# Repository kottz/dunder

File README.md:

# 🖱️ Dunder
A fully* functioning mouse implemented from scratch.

# _**Intended features**_
-----------
- Button functionality built into the scroll wheel - One should be able to click the scroll wheel.
- additional buttons found on the mouse: 
1. Mouse sensitivity buttons - one to increase sensitivity and one to reduce it.
2. forward/back buttons - two macro buttons for the user to bind.

- Led user settings.
- Custom shell. 3D printed.

# _**Design overview**_
-----------

_Buttons provide:_
1. Right and left click.
2. Mouse wheel click.
3. Forward and backwards, which are two macro buttons.
4. Sense up and sense down, two buttons to control mouse sensitivity.

_Sensor provide position data._

_PSU provide:_
1. 3.3V to the buttons and mcu.
2. 1.9V to the sensor.

# _**Circuit design**_
-----------
_**KiCAD diagram**_
-----------

# _**Board design**_
_**KiCAD model**_
-----------

_**3D model**_
-----------

_**Real board**_
-----------
##### Version 1

##### Version 2

# _**Custom case**_
-----------
The case was designed from scratch using Fusion 360.

# _**Demo**_
-----------
##### Demo of mouse functionality

##### Demo of 3D printed case

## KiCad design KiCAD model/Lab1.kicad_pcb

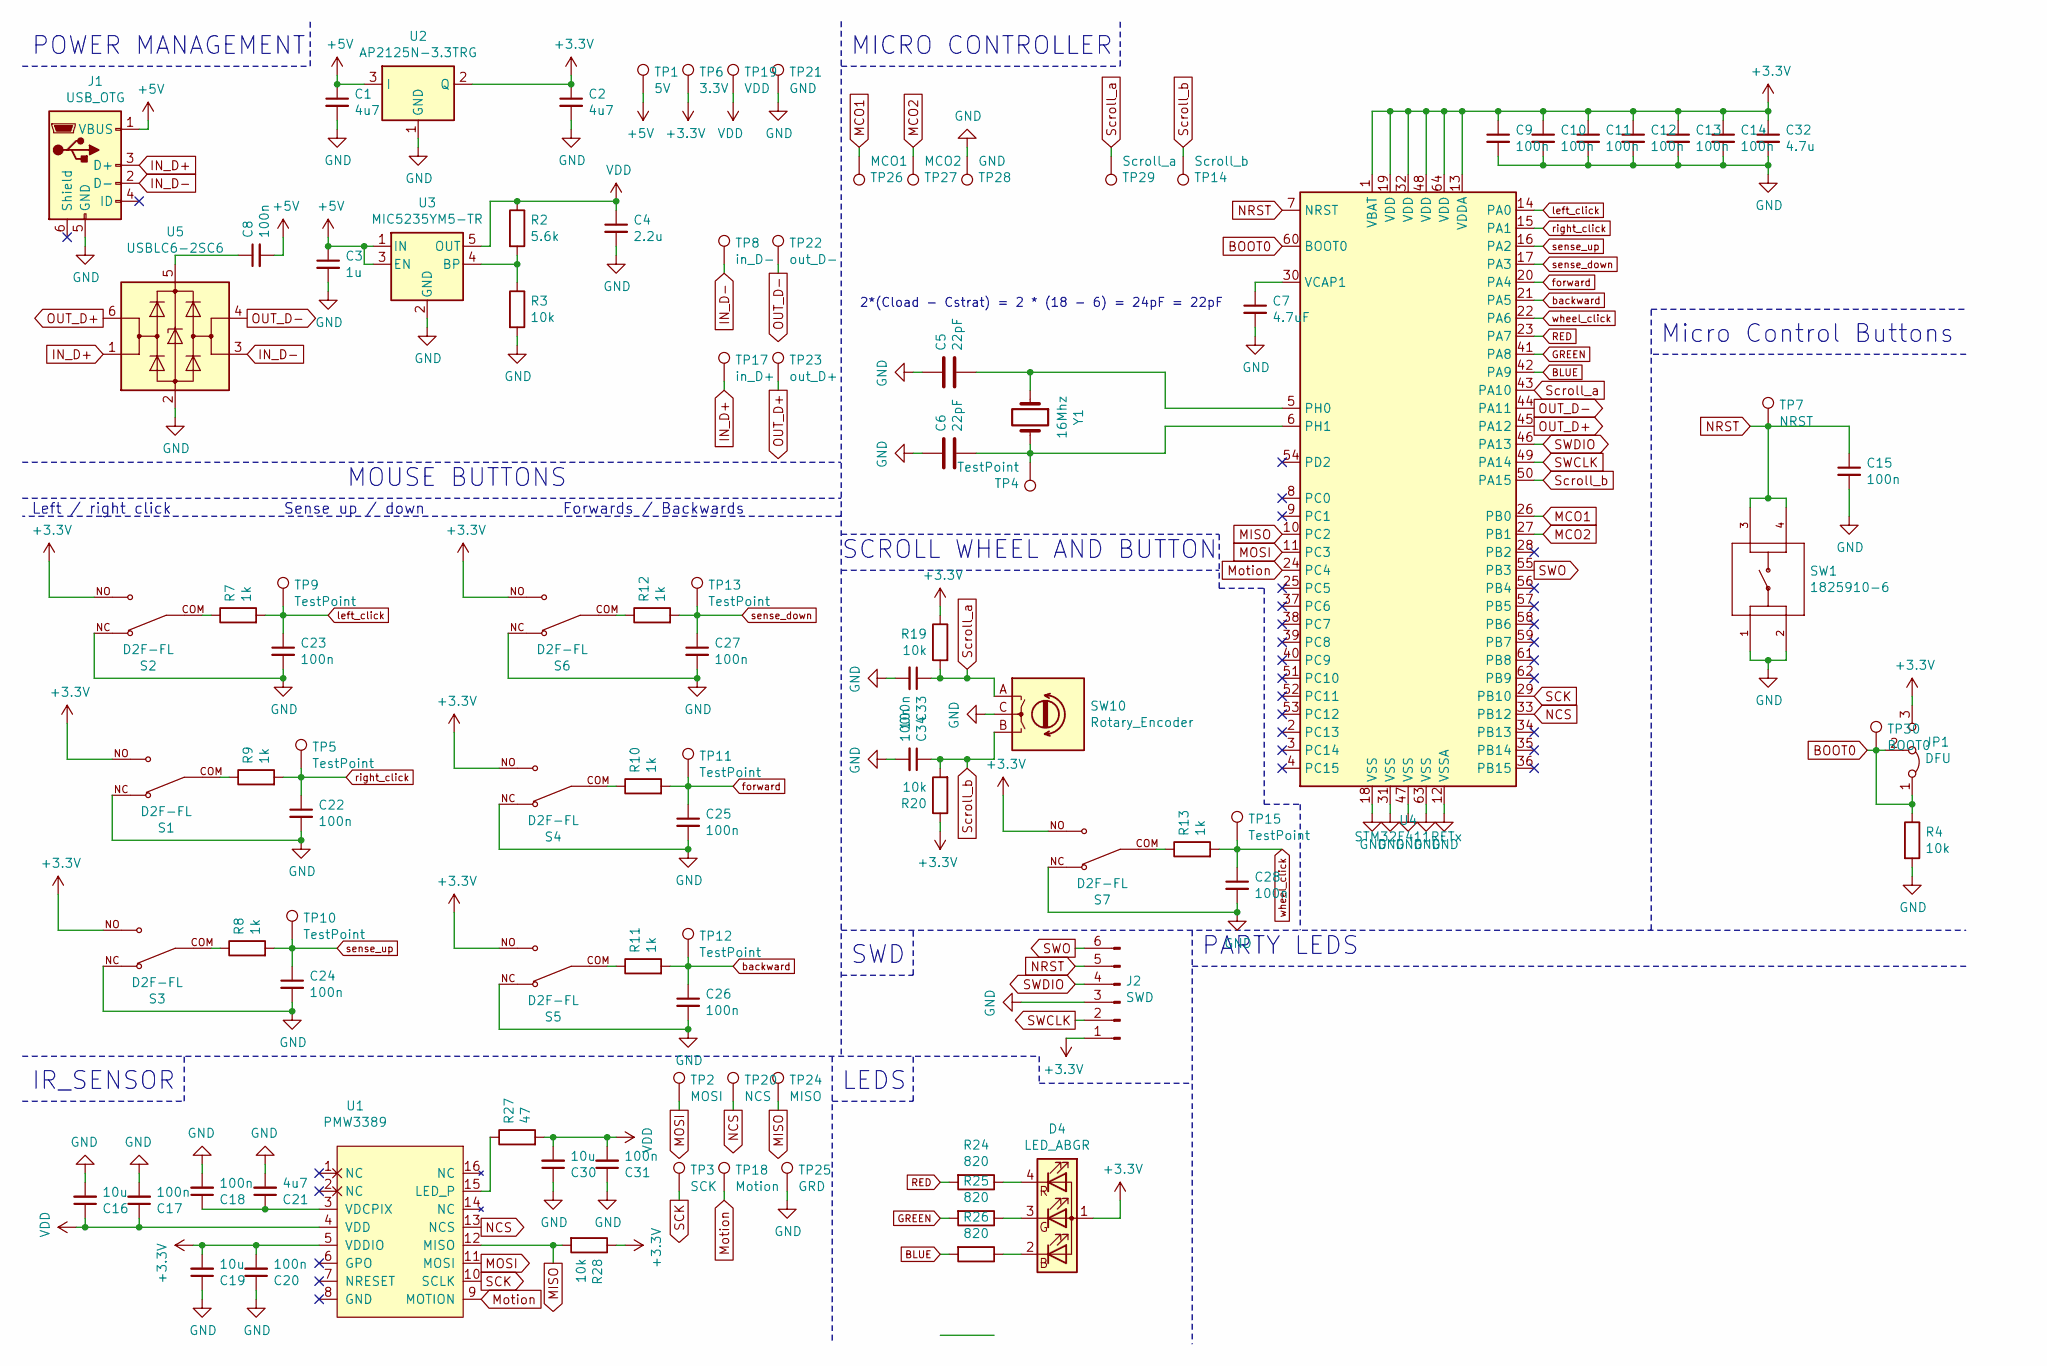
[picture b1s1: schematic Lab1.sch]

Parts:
C1, C2, C21: 4u7; C_0805_2012Metric_Pad1.18x1.45mm_HandSolder
C3: 1u; C_0805_2012Metric_Pad1.18x1.45mm_HandSolder
C4: 2.2u; C_0805_2012Metric_Pad1.18x1.45mm_HandSolder
C5, C6: 22pF; C_0805_2012Metric_Pad1.18x1.45mm_HandSolder
C7: 4.7uF; C_0805_2012Metric_Pad1.18x1.45mm_HandSolder
C8, C9, C10, C11, C12, C13, C14, C15, C17, C18, C20, C22, C23, C24, C25, C26, C27, C28, C31, C33, C34: 100n; C_0805_2012Metric_Pad1.18x1.45mm_HandSolder
C16, C19, C30: 10u; C_0805_2012Metric_Pad1.18x1.45mm_HandSolder
C32: 4.7u; C_0805_2012Metric_Pad1.18x1.45mm_HandSolder
D4: LED_ABGR; LED_RGB_1210_RND_135-00251
J1: USB_OTG; USB_Micro-B_Wuerth_614105150721_Vertical
J2: SWD; PinHeader_1x06_P2.54mm_Vertical
JP1: DFU; PinHeader_1x03_P2.54mm_Vertical
R2: 5.6k; R_0805_2012Metric_Pad1.20x1.40mm_HandSolder
R3, R4, R19, R20, R28: 10k; R_0805_2012Metric_Pad1.20x1.40mm_HandSolder
R7, R8, R9, R10, R11, R12, R13: 1k; R_0805_2012Metric_Pad1.20x1.40mm_HandSolder
R24, R25, R26: 820; R_0805_2012Metric_Pad1.20x1.40mm_HandSolder
R27: 47; R_0805_2012Metric_Pad1.20x1.40mm_HandSolder
S1, S2, S3, S4, S5, S6, S7: D2F-FL; SW_D2F-FL; PARTREV N/A
SW1: 1825910-6; SW_1825910-6-4
SW10: Rotary_Encoder; EC10E1220505
TP1: 5V; TestPoint_Pad_1.5x1.5mm
TP2: MOSI; TestPoint_Pad_1.5x1.5mm
TP3: SCK; TestPoint_Pad_1.5x1.5mm
TP4, TP5, TP9, TP10, TP11, TP12, TP13, TP15: TestPoint; TestPoint_Pad_1.5x1.5mm
TP6: 3.3V; TestPoint_Pad_1.5x1.5mm
TP7: NRST; TestPoint_Pad_1.5x1.5mm
TP8: in_D-; TestPoint_Pad_1.5x1.5mm
TP14: Scroll_b; TestPoint_Pad_1.5x1.5mm
TP17: in_D+; TestPoint_Pad_1.5x1.5mm
TP18: Motion; TestPoint_Pad_1.5x1.5mm
TP19: VDD; TestPoint_Pad_1.5x1.5mm
TP20: NCS; TestPoint_Pad_1.5x1.5mm
TP21, TP28: GND; TestPoint_Pad_1.5x1.5mm
TP22: out_D-; TestPoint_Pad_1.5x1.5mm
TP23: out_D+; TestPoint_Pad_1.5x1.5mm
TP24: MISO; TestPoint_Pad_1.5x1.5mm
TP25: GRD; TestPoint_Pad_1.5x1.5mm
TP26: MCO1; TestPoint_Pad_1.5x1.5mm
TP27: MCO2; TestPoint_Pad_1.5x1.5mm
TP29: Scroll_a; TestPoint_Pad_1.5x1.5mm
TP30: BOOT0; TestPoint_Pad_1.5x1.5mm
U1: PMW3389
U2: AP2125N-3.3TRG; SOT-23_Handsoldering
U3: MIC5235YM5-TR; SOT-23-5_HandSoldering
U4: STM32F411RETx; LQFP-64_10x10mm_P0.5mm
U5: USBLC6-2SC6; SOT-23-6
Y1: 16Mhz; Crystal_SMD_HC49-SD_HandSoldering

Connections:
+3V3: C2.1, C9.1, C10.1, C11.1, C12.1, C13.1, C14.1, C19.2, C20.2, C32.1, D4.1 (A), J2.1, JP1.3 (B), R19.1, R20.1, R28.1, S1.NO, S2.NO, S3.NO, S4.NO, S5.NO, S6.NO, S7.NO, TP6.1, U1.5 (VDDIO), U2.2 (Q), U4.1 (VBAT), U4.13 (VDDA), U4.19 (VDD), U4.32 (VDD), U4.48 (VDD), U4.64 (VDD)
+5V: C1.1, C3.1, C8.2, J1.1 (VBUS), TP1.1, U2.3 (I), U3.1 (IN), U3.3 (EN)
BLUE: R26.2, U4.42 (PA9)
BOOT0: JP1.1 (A), JP1.2 (C), R4.1, TP30.1, U4.60 (BOOT0)
GND: C1.2, C2.2, C3.2, C4.2, C5.1, C6.1, C7.2, C9.2, C10.2, C11.2, C12.2, C13.2, C14.2, C15.2, C16.2, C17.2, C18.2, C19.1, C20.1, C21.2, C22.2, C23.2, C24.2, C25.2, C26.2, C27.2, C28.2, C30.1, C31.1, C32.2, C33.2, C34.2, J1.5 (GND), J2.3, R3.2, R4.2, S1.NC, S2.NC, S3.NC, S4.NC, S5.NC, S6.NC, S7.NC, SW1.1, SW1.2, SW10.C, TP21.1, TP25.1, TP28.1, U2.1 (GND), U3.2 (GND), U4.12 (VSSA), U4.18 (VSS), U4.31 (VSS), U4.47 (VSS), U4.63 (VSS), U5.2 (GND)
GREEN: R25.2, U4.41 (PA8)
IN_D+: J1.3 (D+), TP17.1, U5.1 (I/O1)
IN_D-: J1.2 (D-), TP8.1, U5.3 (I/O2)
MCO1: TP26.1, U4.26 (PB0)
MCO2: TP27.1, U4.27 (PB1)
MISO: R28.2, TP24.1, U1.12 (MISO), U4.10 (PC2)
MOSI: TP2.1, U1.11 (MOSI), U4.11 (PC3)
Motion: TP18.1, U1.9 (MOTION), U4.24 (PC4)
NCS: TP20.1, U1.13 (NCS), U4.33 (PB12)
NRST: C15.1, J2.5, SW1.3, SW1.4, TP7.1, U4.7 (NRST)
unnamed: C5.2, U4.5 (PH0), Y1.1
unnamed: C6.2, TP4.1, U4.6 (PH1), Y1.2
unnamed: C7.1, U4.30 (VCAP1)
unnamed: C8.1, U5.5 (VBUS)
unnamed: C18.1, C21.1, U1.3 (VDCPIX)
unnamed: D4.2 (BK), R26.1
unnamed: D4.3 (GK), R25.1
unnamed: D4.4 (RK), R24.1
unnamed: R2.2, R3.1, U3.4 (BP)
unnamed: R7.1, S2.COM
unnamed: R8.1, S3.COM
unnamed: R9.1, S1.COM
unnamed: R10.1, S4.COM
unnamed: R11.1, S5.COM
unnamed: R12.1, S6.COM
unnamed: R13.1, S7.COM
unnamed: R27.1, U1.15 (LED_P)
OUT_D+: TP23.1, U4.45 (PA12), U5.6 (I/O1)
OUT_D-: TP22.1, U4.44 (PA11), U5.4 (I/O2)
RED: R24.2, U4.23 (PA7)
SCK: TP3.1, U1.10 (SCLK), U4.29 (PB10)
SWCLK: J2.2, U4.49 (PA14)
SWDIO: J2.4, U4.46 (PA13)
SWO: J2.6, U4.55 (PB3)
Scroll_a: C33.1, R19.2, SW10.A, TP29.1, U4.43 (PA10)
Scroll_b: C34.1, R20.2, SW10.B, TP14.1, U4.50 (PA15)
VDD: C4.1, C16.1, C17.1, C30.2, C31.2, R2.1, R27.2, TP19.1, U1.4 (VDD), U3.5 (OUT)
backward: C26.1, R11.2, TP12.1, U4.21 (PA5)
forward: C25.1, R10.2, TP11.1, U4.20 (PA4)
left_click: C23.1, R7.2, TP9.1, U4.14 (PA0)
right_click: C22.1, R9.2, TP5.1, U4.15 (PA1)
sense_down: C27.1, R12.2, TP13.1, U4.17 (PA3)
sense_up: C24.1, R8.2, TP10.1, U4.16 (PA2)
wheel_click: C28.1, R13.2, TP15.1, U4.22 (PA6)

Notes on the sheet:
2*(Cload - Cstrat) = 2 * (18 - 6) = 24pF = 22pF
MICRO CONTROLLER
IR_SENSOR
Micro Control Buttons
POWER MANAGEMENT
MOUSE BUTTONS
Forwards / Backwards
Sense up / down
Left / right click
PARTY LEDS
LEDS
SWD
SCROLL WHEEL AND BUTTON

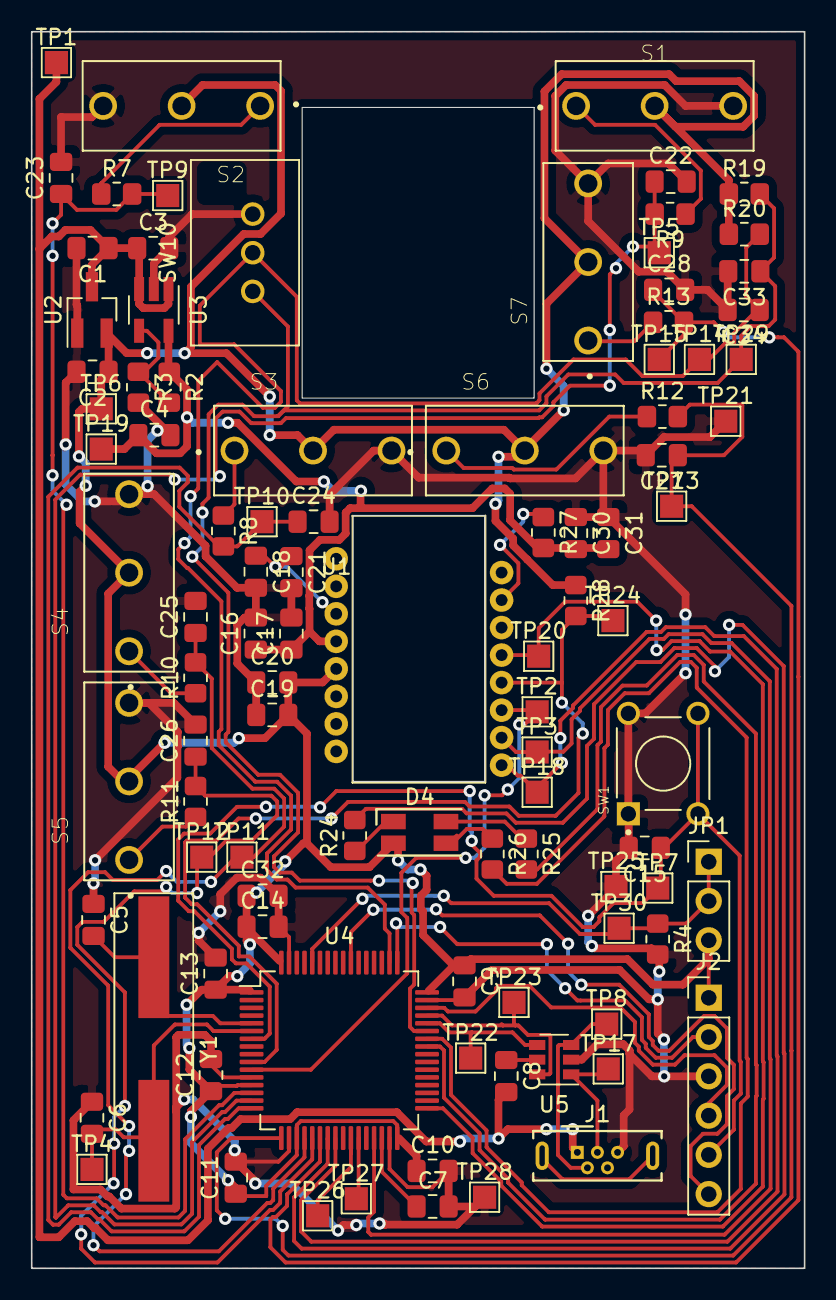
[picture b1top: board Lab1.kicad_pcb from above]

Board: 2 copper layers, 50.0 x 80.0 mm, 98 parts (0 on the bottom side), 49 nets.

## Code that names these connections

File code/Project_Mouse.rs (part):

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use stm32f4xx_hal::{
    gpio::Speed,
    gpio::{
        gpiob::{PB10, PB12},
        gpioc::{PC2, PC3},
        Alternate, Output, PushPull,
    },
    spi::Spi,
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    Spi<
        stm32f4xx_hal::stm32::SPI2,
        (
            PB10<Alternate<stm32f4xx_hal::gpio::AF5>>,
            PC2<Alternate<stm32f4xx_hal::gpio::AF5>>,
            PC3<Alternate<stm32f4xx_hal::gpio::AF5>>,
        ),
    >,
    PB12<Output<PushPull>>,
>;
use rtt_target::{rprintln, rtt_init_print};

use stm32f4xx_hal::{
    gpio::{gpioa::PA7, gpioa::PA8, gpioa::PA9},
    gpio::{gpioa::PA0, gpioa::PA1, gpioa::PA2, gpioa::PA3, gpioa::PA4, gpioa::PA5, gpioa::PA6, gpioa::PA10, gpioa::PA15, Input, PullUp},
};

const OFFSET: u32 = 1_000_000;
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        hid: HIDClass<'static, UsbBusType>,
        usb_dev: UsbDevice<'static, UsbBusType>,
        pmw3389: PMW3389T,
        led_r: PA7<Output<PushPull>>,
        led_g: PA8<Output<PushPull>>,
        led_b: PA9<Output<PushPull>>,
        r_click: PA1<Input<PullUp>>,
        l_click: PA0<Input<PullUp>>,
        w_click: PA6<Input<PullUp>>,
        M1_click: PA4<Input<PullUp>>,
        M2_click: PA5<Input<PullUp>>,
        scl_plus: PA2<Input<PullUp>>,
        scl_minus: PA3<Input<PullUp>>,
        scroll_up: PA10<Input<PullUp>>,
        scroll_down: PA15<Input<PullUp>>,
        Scaler: f32,
        Counter: u8,
        Led_Counter: u16,
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            usb_global: cx.device.OTG_FS_GLOBAL,
            usb_device: cx.device.OTG_FS_DEVICE,
            usb_pwrclk: cx.device.OTG_FS_PWRCLK,
            pin_dm: gpioa.pa11.into_alternate_af10(),
            pin_dp: gpioa.pa12.into_alternate_af10(),
        };
	
        USB_BUS.replace(UsbBus::new(usb, EP_MEMORY));
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        let gpiob = cx.device.GPIOB.split();
        let gpioc = cx.device.GPIOC.split();

        let sck = gpiob.pb10.into_alternate_af5();
        let miso = gpioc.pc2.into_alternate_af5();
        let mosi = gpioc.pc3.into_alternate_af5();
        let cs = gpiob.pb12.into_push_pull_output().set_speed(Speed::High);

        let spi = Spi::spi2(
            cx.device.SPI2,
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        init::LateResources {
            hid,
            usb_dev,
            led_r: gpioa.pa7.into_push_pull_output(),
            led_g: gpioa.pa8.into_push_pull_output(),
            led_b: gpioa.pa9.into_push_pull_output(),
            r_click: gpioa.pa1.into_pull_up_input(),
            l_click: gpioa.pa0.into_pull_up_input(),
            w_click: gpioa.pa6.into_pull_up_input(),
            M1_click: gpioa.pa4.into_pull_up_input(),
            M2_click: gpioa.pa5.into_pull_up_input(),
            scl_plus: gpioa.pa2.into_pull_up_input(),
            scl_minus: gpioa.pa3.into_pull_up_input(),
            scroll_up: gpioa.pa10.into_pull_up_input(),
            scroll_down: gpioa.pa15.into_pull_up_input(),
            Scaler: scaler,
            Counter: 0,
            Led_Counter: 0,
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
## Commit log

2021-01-28 add initial design diagram
2021-02-04 Initial upload for KiCAD model
2021-02-10 Improved design and fixed rotary encoder
2021-02-11 Components checked,basic layout of components fixed
2021-02-11 orgot the model
2021-02-11 Fixed footprint for testpoints
2021-02-11 added component list
2021-02-14 final pcb design
2021-02-14 Update USB connector and Encoder
2021-02-14 Update testpoints
2021-02-14 add BOM
2021-03-26 Upload New File
2021-03-26 Add new directory
2021-03-26 Replace Gaming_Mouse.jpg
2021-03-26 fix swdio/swclk + usb issue
2021-04-28 add sensor + scroll wheel support
2021-05-07 fix leds + cleanup
2021-05-26 set led to csgo mode + fix default sensor config
2021-05-26 add board v2
2021-05-26 add 3D case f360 project + renders
2021-05-26 update README with latest updates and demos
2021-05-26 fix formatting error in README
2024-09-02 update todo
2024-09-02 update changelog
